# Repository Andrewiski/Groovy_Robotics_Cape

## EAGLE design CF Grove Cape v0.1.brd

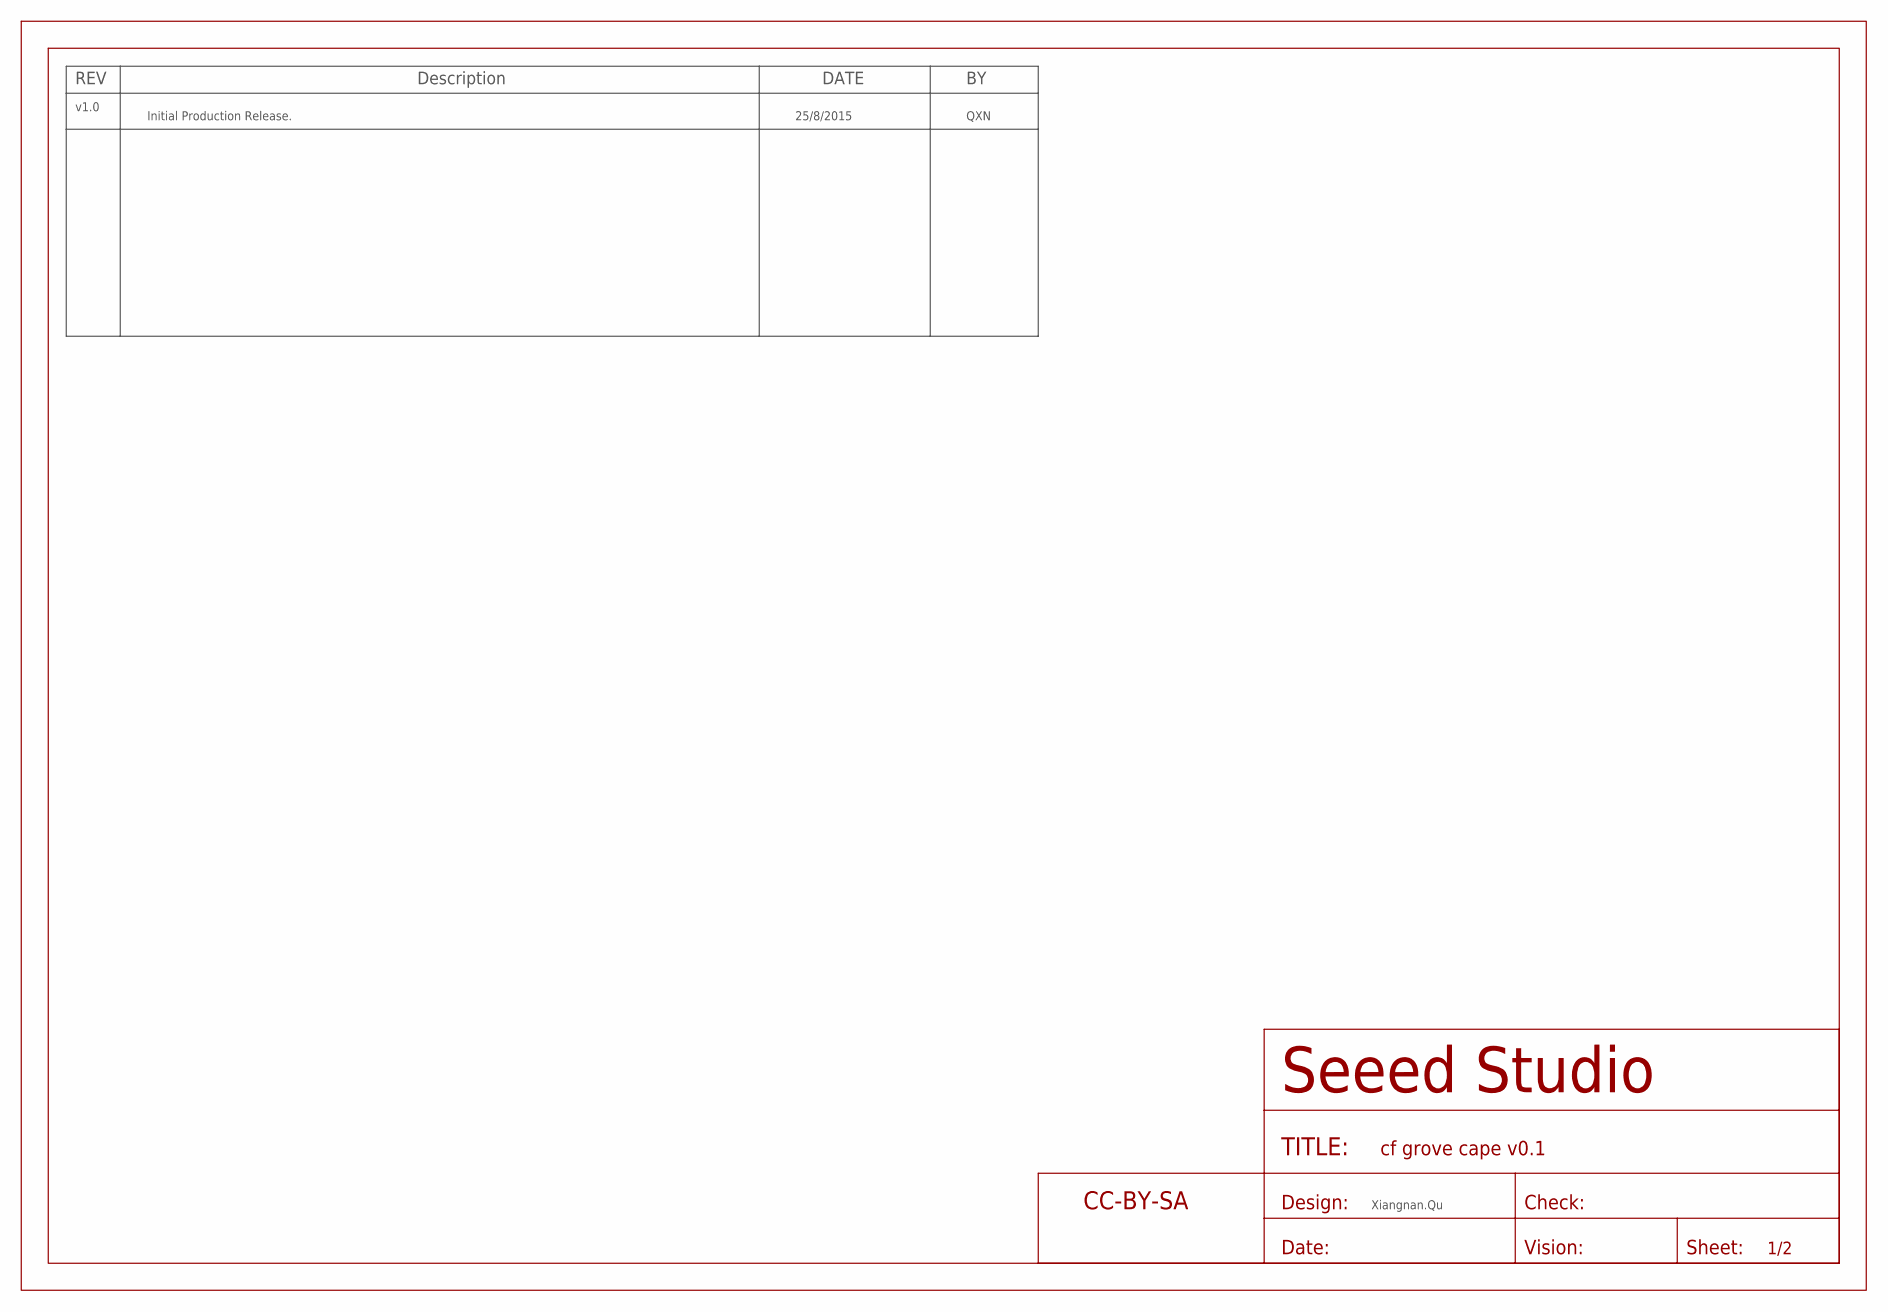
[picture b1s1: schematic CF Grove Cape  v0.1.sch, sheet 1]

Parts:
FR1: SEEEDSTUDIO-OPEN-SCH-FRAME; SEEEDSTUDIO-PCB-FRAME

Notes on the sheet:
REV
Description
DATE
v1.0
Initial Production Release.
25/8/2015
QXN
Xiangnan.Qu

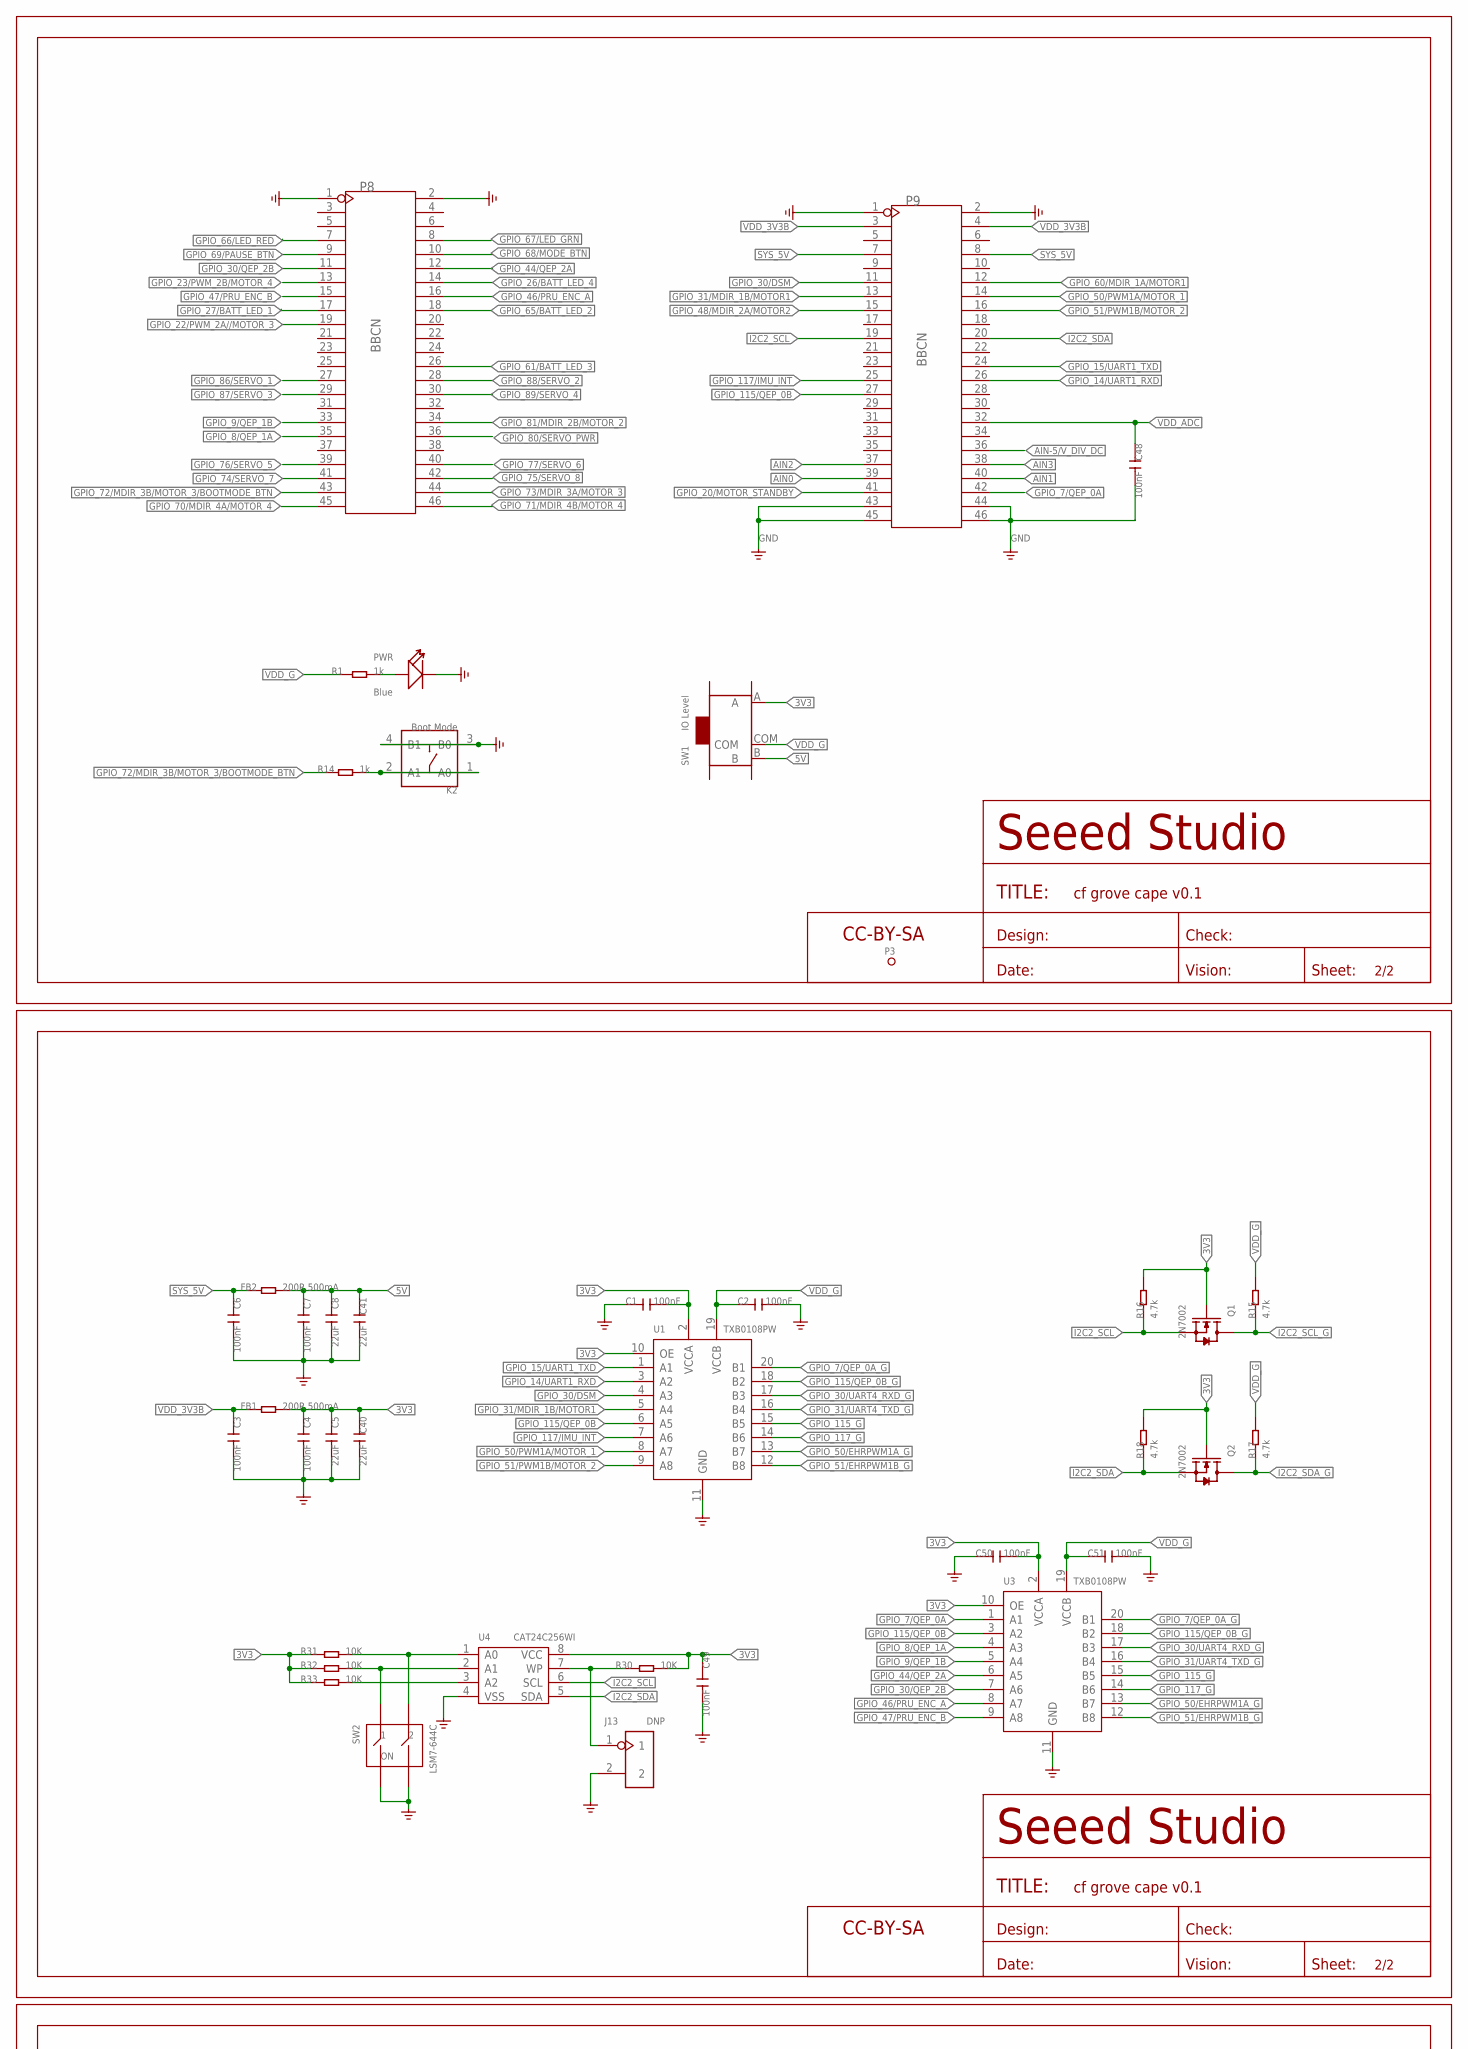
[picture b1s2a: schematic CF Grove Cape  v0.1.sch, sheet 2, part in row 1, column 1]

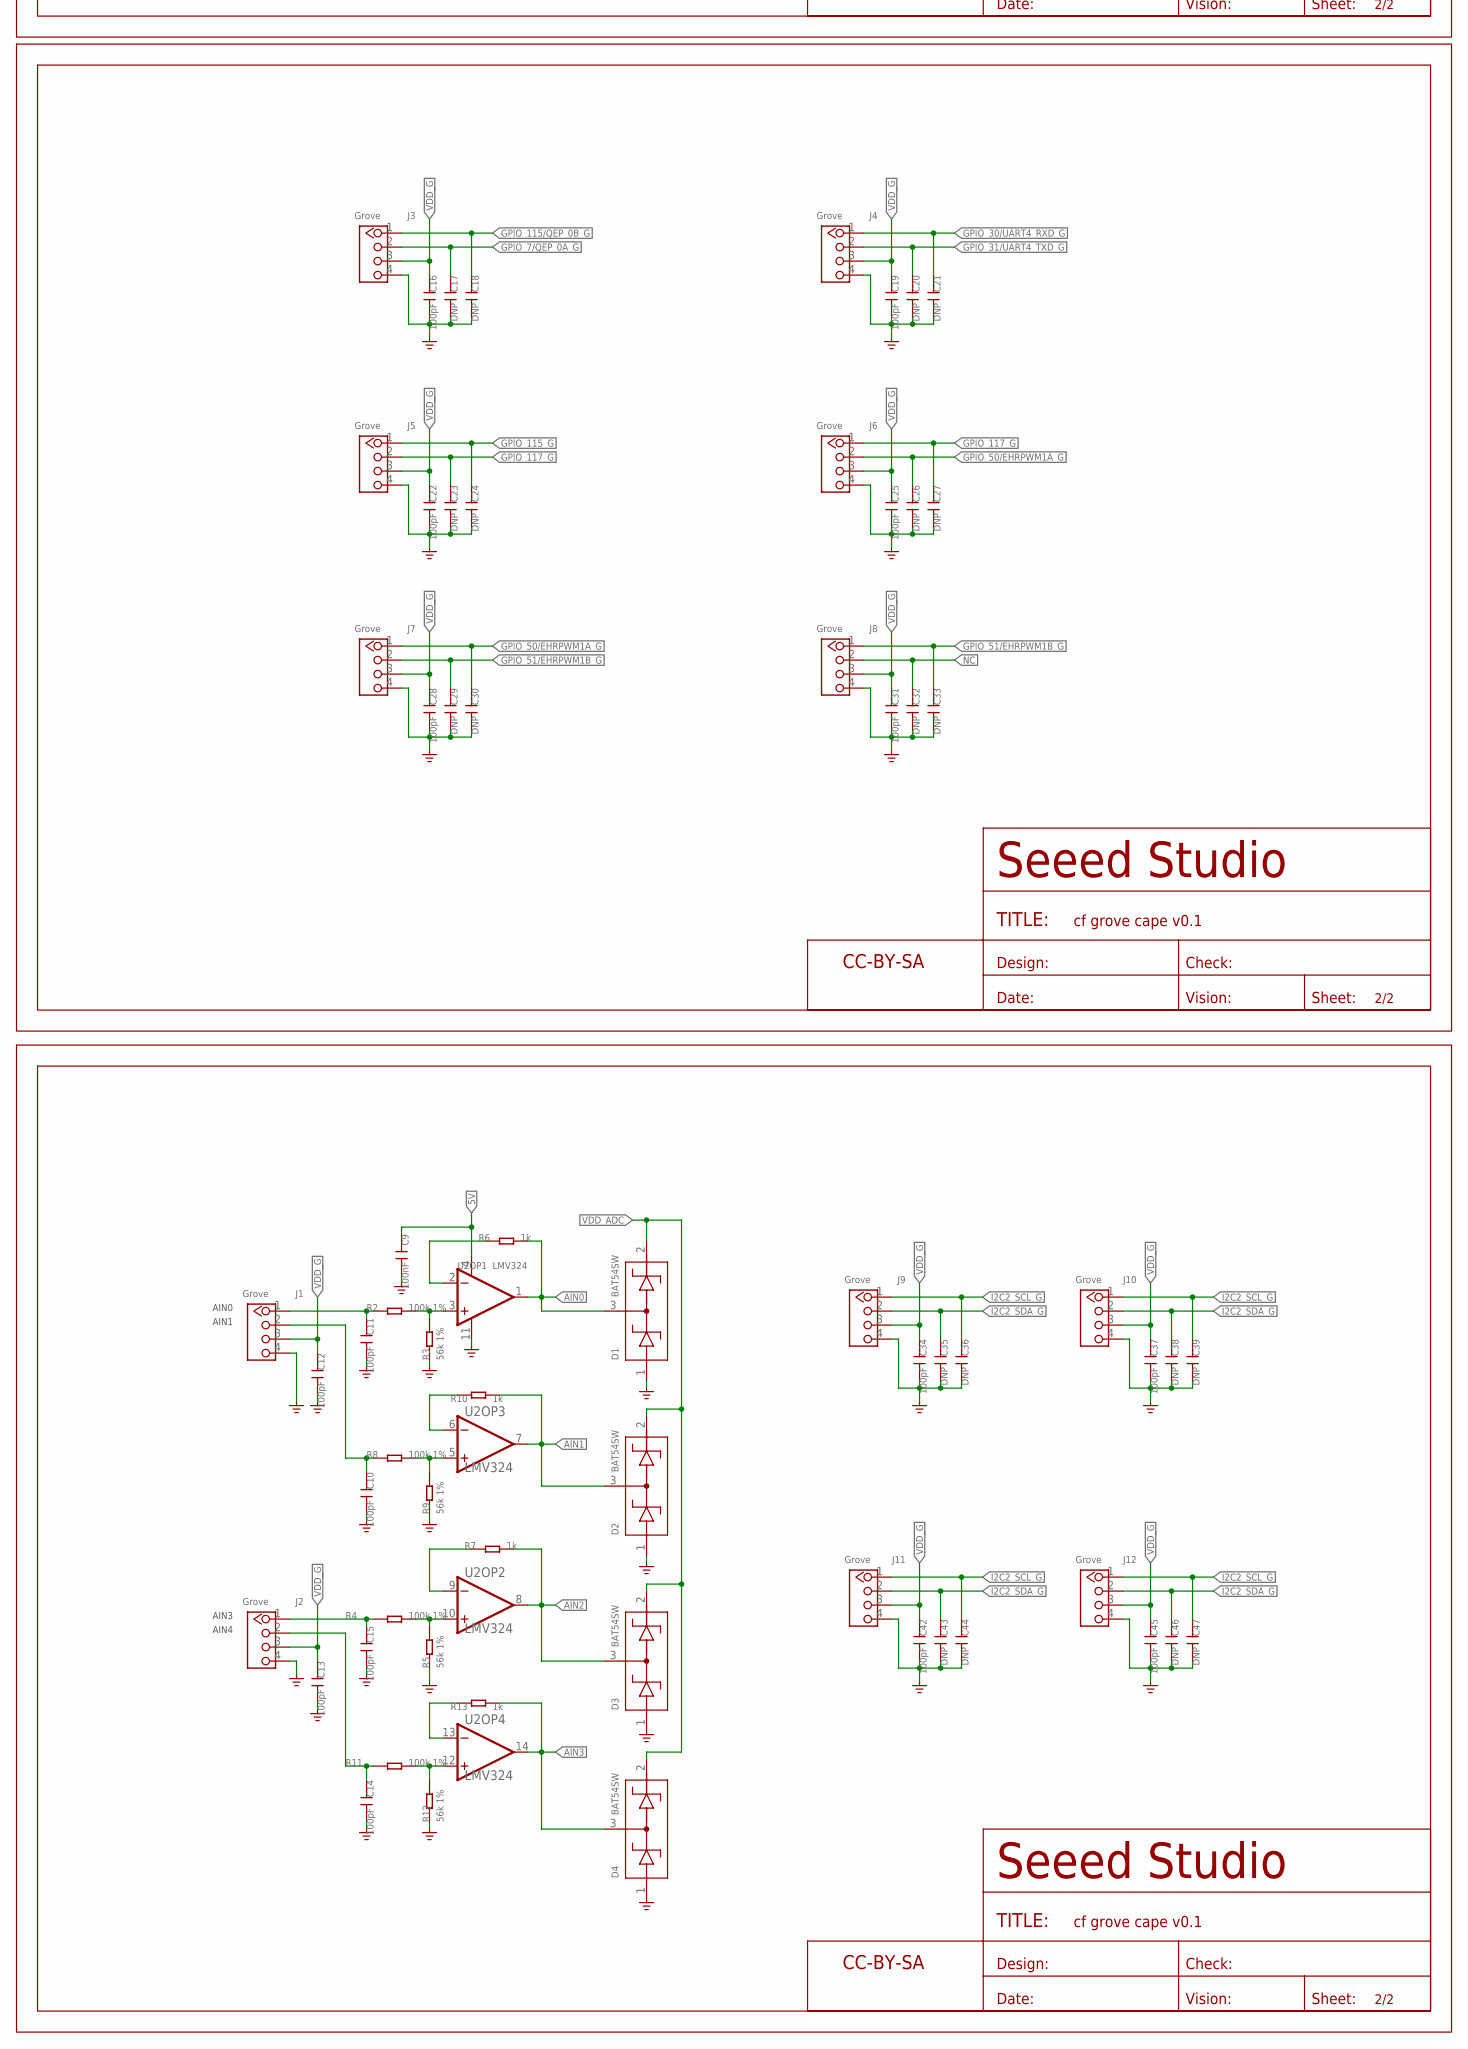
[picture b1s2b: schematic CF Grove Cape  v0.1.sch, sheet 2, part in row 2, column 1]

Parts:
C1, C2, C3, C4, C6, C7, C9, C48, C49, C50, C51: 100nF; C0402
C5, C8, C40, C41: 22uF; C0805
C10, C11, C12, C13, C14, C15, C16, C19, C22, C25, C28, C31, C34, C37, C42, C45: 100pF; C0402
C17, C18, C20, C21, C23, C24, C26, C27, C29, C30, C32, C33, C35, C36, C38, C39, C43, C44, C46, C47: DNP; C0402
D1, D2, D3, D4: BAT54SW; SOT-23
FB1, FB2: 200R 500mA; R0603
FR2, FR3, FR4, FR5: SEEEDSTUDIO-OPEN-SCH-FRAME; SEEEDSTUDIO-PCB-FRAME
J1, J2, J3, J4, J5, J6, J7, J8, J9, J10, J11, J12: Grove; HW4-2.0
J13: DNP; H2-1.5
K2: Boot Mode; SW4P-SMD-4.5X3.2X2.5MM
P3: MARK-1.0'ANNULAR'; ROUND-MARK-1.0
P8, P9: BBCN; 2X23P-2.54
PWR: Blue; LED-0402
Q1, Q2: 2N7002; SOT-23
R1, R6, R7, R10, R13, R14: 1k; R0402
R2, R4, R8, R11: 100k 1%; R0402
R3, R5, R9, R12: 56k 1%; R0402
R15, R16, R17, R18: 4.7k; R0402
R30, R31, R32, R33: 10K; R0402
SW1: IO Level; SW7-SMD-L6.7X2.7X3.2MM
SW2: LSM7-644C; SW4-SMD-5.08X6.8X3.3MM
U1, U3: TXB0108PW; TSSOP20-0.65-6.5X4.4MM
U2: LMV324; TSSOP14-0.65-5X4.4MM
U4: CAT24C256WI; SOIC8-1.27-5X4MM

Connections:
3V3: C1.2, C4.1, C5.1, C40.1, C49.2, C50.2, FB1.2, Q1.1 (G), Q2.1 (G), R16.2, R18.2, R30.1, R31.2, R32.2, R33.2, SW1.A, U1.2 (VCCA), U1.10 (OE), U3.2 (VCCA), U3.10 (OE), U4.8 (VCC)
5V: C7.1, C8.1, C9.1, C41.1, FB2.2, SW1.B, U2.4 (V+)
AIN0: D1.3, P9.39, R6.2, U2.1 (OUT)
AIN1: D2.3, P9.40, R10.2, U2.7 (OUT)
AIN2: D3.3, P9.37, R7.2, U2.8 (OUT)
AIN3: D4.3, P9.38, R13.2, U2.14 (OUT)
AIN-5/V_DIV_DC: P9.36
GND: C1.1, C2.2, C3.2, C4.2, C5.2, C6.2, C7.2, C8.2, C9.2, C10.2, C11.2, C12.2, C13.2, C14.2, C15.2, C16.2, C17.2, C18.2, C19.2, C20.2, C21.2, C22.2, C23.2, C24.2, C25.2, C26.2, C27.2, C28.2, C29.2, C30.2, C31.2, C32.2, C33.2, C34.2, C35.2, C36.2, C37.2, C38.2, C39.2, C40.2, C41.2, C42.2, C43.2, C44.2, C45.2, C46.2, C47.2, C48.2, C49.1, C50.1, C51.2, D1.1, D2.1, D3.1, D4.1, J1.4, J2.4, J3.4, J4.4, J5.4, J6.4, J7.4, J8.4, J9.4, J10.4, J11.4, J12.4, J13.2, K2.3 (B0), K2.4 (B1), P8.1, P8.2, P9.1, P9.2, P9.43, P9.44, P9.45, P9.46, PWR.-, R3.1, R5.1, R9.1, R12.1, SW2.3, SW2.4, U1.11 (GND), U2.11 (V-), U3.11 (GND), U4.4 (VSS)
GPIO_7/QEP_0A: P9.42, U3.1 (A1)
GPIO_7/QEP_0A_G: C17.1, J3.2, U1.20 (B1), U3.20 (B1)
GPIO_8/QEP_1A: P8.35, U3.4 (A3)
GPIO_9/QEP_1B: P8.33, U3.5 (A4)
GPIO_14/UART1_RXD: P9.26, U1.3 (A2)
GPIO_15/UART1_TXD: P9.24, U1.1 (A1)
GPIO_20/MOTOR_STANDBY: P9.41
GPIO_22/PWM_2A//MOTOR_3: P8.19
GPIO_23/PWM_2B/MOTOR_4: P8.13
GPIO_26/BATT_LED_4: P8.14
GPIO_27/BATT_LED_1: P8.17
GPIO_30/DSM: P9.11, U1.4 (A3)
GPIO_30/QEP_2B: P8.11, U3.7 (A6)
GPIO_30/UART4_RXD_G: C21.1, J4.1, U1.17 (B3), U3.17 (B3)
GPIO_31/MDIR_1B/MOTOR1: P9.13, U1.5 (A4)
GPIO_31/UART4_TXD_G: C20.1, J4.2, U1.16 (B4), U3.16 (B4)
GPIO_44/QEP_2A: P8.12, U3.6 (A5)
GPIO_46/PRU_ENC_A: P8.16, U3.8 (A7)
GPIO_47/PRU_ENC_B: P8.15, U3.9 (A8)
GPIO_48/MDIR_2A/MOTOR2: P9.15
GPIO_50/EHRPWM1A_G: C26.1, C30.1, J6.2, J7.1, U1.13 (B7), U3.13 (B7)
GPIO_50/PWM1A/MOTOR_1: P9.14, U1.8 (A7)
GPIO_51/EHRPWM1B_G: C29.1, C33.1, J7.2, J8.1, U1.12 (B8), U3.12 (B8)
GPIO_51/PWM1B/MOTOR_2: P9.16, U1.9 (A8)
GPIO_60/MDIR_1A/MOTOR1: P9.12
GPIO_61/BATT_LED_3: P8.26
GPIO_65/BATT_LED_2: P8.18
GPIO_66/LED_RED: P8.7
GPIO_67/LED_GRN: P8.8
GPIO_68/MODE_BTN: P8.10
GPIO_69/PAUSE_BTN: P8.9
GPIO_70/MDIR_4A/MOTOR_4: P8.45
GPIO_71/MDIR_4B/MOTOR_4: P8.46
GPIO_72/MDIR_3B/MOTOR_3/BOOTMODE_BTN: P8.43, R14.1
GPIO_73/MDIR_3A/MOTOR_3: P8.44
GPIO_74/SERVO_7: P8.41
GPIO_75/SERVO_8: P8.42
GPIO_76/SERVO_5: P8.39
GPIO_77/SERVO_6: P8.40
GPIO_80/SERVO_PWR: P8.36
GPIO_81/MDIR_2B/MOTOR_2: P8.34
GPIO_86/SERVO_1: P8.27
GPIO_87/SERVO_3: P8.29
GPIO_88/SERVO_2: P8.28
GPIO_89/SERVO_4: P8.30
GPIO_115/QEP_0B: P9.27, U1.6 (A5), U3.3 (A2)
GPIO_115/QEP_0B_G: C18.1, J3.1, U1.18 (B2), U3.18 (B2)
GPIO_115_G: C24.1, J5.1, U1.15 (B5), U3.15 (B5)
GPIO_117/IMU_INT: P9.25, U1.7 (A6)
GPIO_117_G: C23.1, C27.1, J5.2, J6.1, U1.14 (B6), U3.14 (B6)
I2C2_SCL: P9.19, Q1.2 (S), R16.1, U4.6 (SCL)
I2C2_SCL_G: C36.1, C39.1, C44.1, C47.1, J9.1, J10.1, J11.1, J12.1, Q1.3 (D), R15.1
I2C2_SDA: P9.20, Q2.2 (S), R18.1, U4.5 (SDA)
I2C2_SDA_G: C35.1, C38.1, C43.1, C46.1, J9.2, J10.2, J11.2, J12.2, Q2.3 (D), R17.1
unnamed: R31.1, SW2.2, U4.1 (A0)
unnamed: R32.1, SW2.1, U4.2 (A1)
unnamed: K2.1 (A0), K2.2 (A1), R14.2
unnamed: PWR.+, R1.2
unnamed: R2.2, R3.2, U2.3 (IN+)
unnamed: R4.2, R5.2, U2.10 (IN+)
unnamed: C11.1, J1.1, R2.1
unnamed: R6.1, U2.2 (IN-)
unnamed: J13.1, R30.2, U4.7 (WP)
unnamed: C15.1, J2.1, R4.1
unnamed: R7.1, U2.9 (IN-)
unnamed: R33.1, U4.3 (A2)
unnamed: C14.1, J2.2, R11.1
unnamed: R11.2, R12.2, U2.12 (IN+)
unnamed: C10.1, J1.2, R8.1
unnamed: R8.2, R9.2, U2.5 (IN+)
unnamed: R10.1, U2.6 (IN-)
unnamed: R13.1, U2.13 (IN-)
NC: C32.1, J8.2
SYS_5V: C6.1, FB2.1, P9.7, P9.8
VDD_3V3B: C3.1, FB1.1, P9.3, P9.4
VDD_ADC: C48.1, D1.2, D2.2, D3.2, D4.2, P9.32
VDD_G: C2.1, C12.1, C13.1, C16.1, C19.1, C22.1, C25.1, C28.1, C31.1, C34.1, C37.1, C42.1, C45.1, C51.1, J1.3, J2.3, J3.3, J4.3, J5.3, J6.3, J7.3, J8.3, J9.3, J10.3, J11.3, J12.3, R1.1, R15.2, R17.2, SW1.COM, U1.19 (VCCB), U3.19 (VCCB)

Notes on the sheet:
AIN0
AIN1
AIN3
AIN4

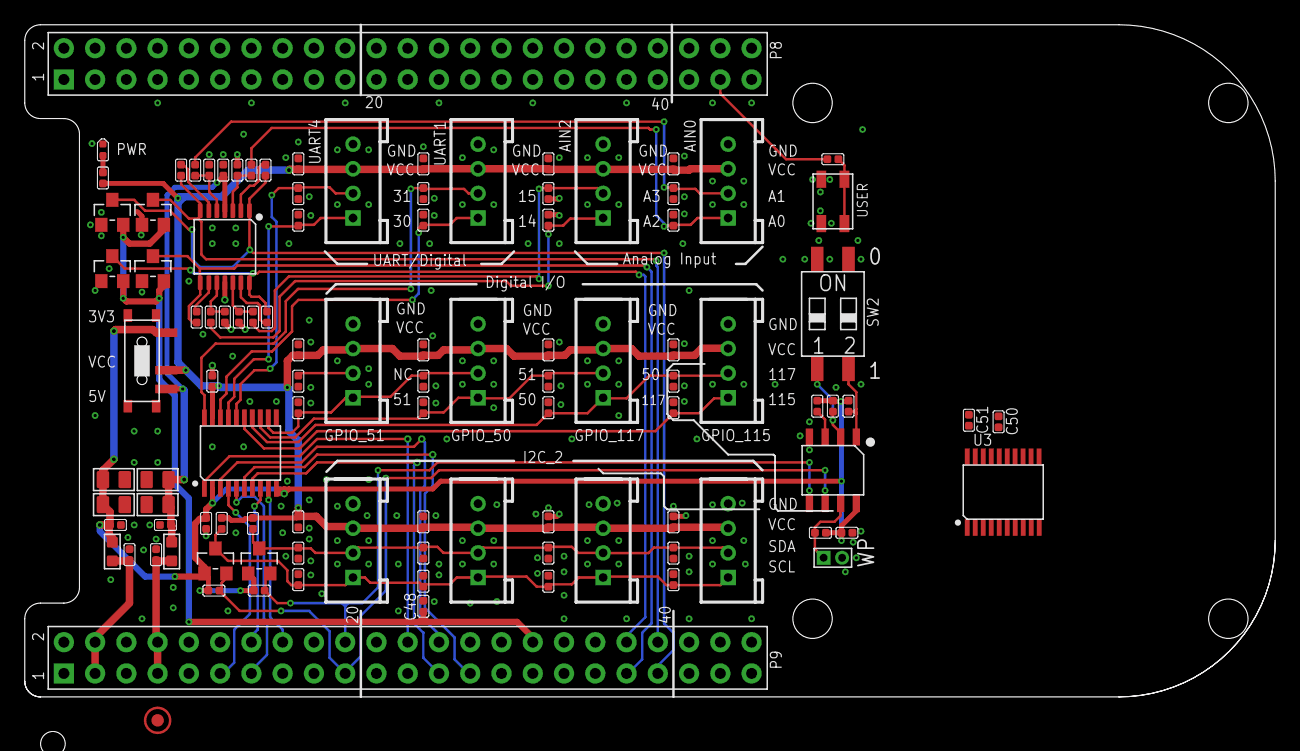
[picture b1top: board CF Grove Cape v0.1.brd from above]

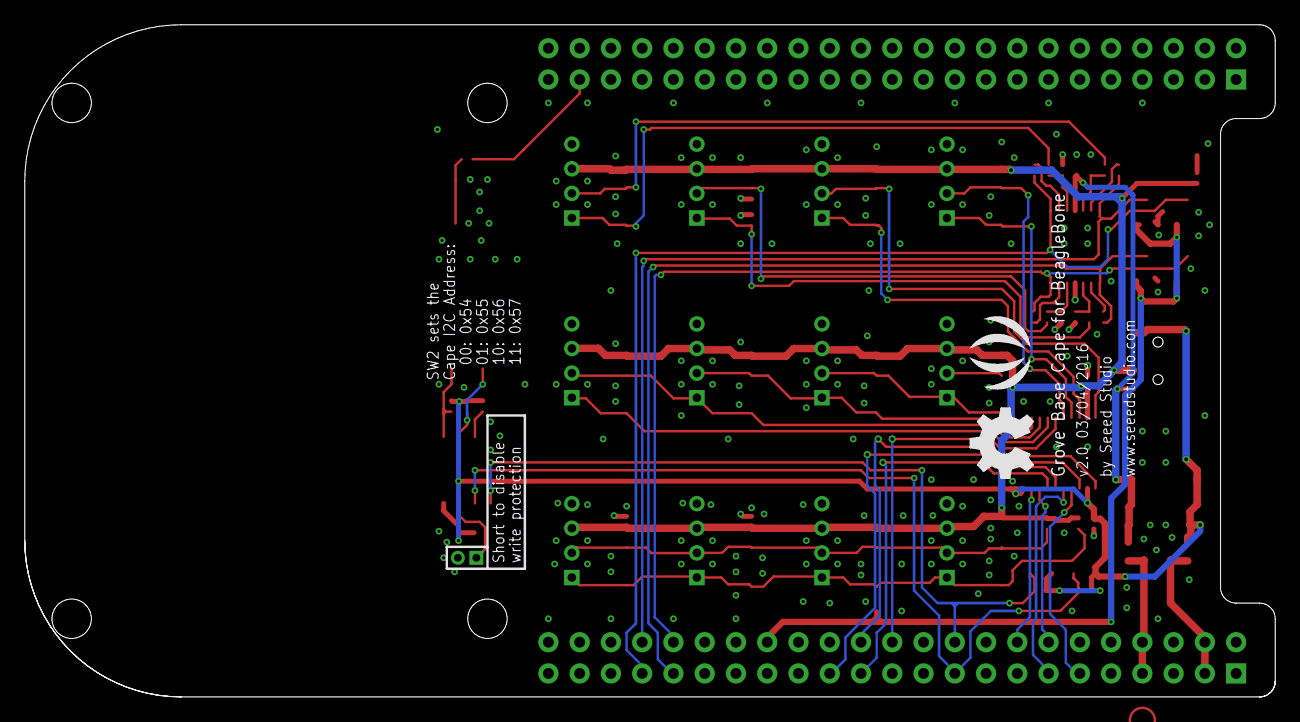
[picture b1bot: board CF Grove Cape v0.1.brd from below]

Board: 2 copper layers, 101.6 x 54.6 mm, 116 parts (2 on the bottom side), 58 nets.

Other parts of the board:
U$16: SEEED-SILK-280*268MIL
U$18: OSHW_FILLX200_NOTEXT
U$26, U$27, U$50, U$51: HOLE-3.2/7.0

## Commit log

2017-05-09 Groovy Cap Intial checkin

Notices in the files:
parts and their libraries:
moudle-new: This work is licensed under the Creative Commons Attribution 4.0 International License.
To view a copy of this license,visit:
http://creativecommons.org/licenses/by-sa/4.0
moudle-new: CC-BY-SA
